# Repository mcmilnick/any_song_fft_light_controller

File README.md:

# any_song_light_controller
Send any song to a Pi, analyze the frequency spectrum, and control light strips.

This project goes with a walkthrough on my website...
https://techtures.wordpress.com/nicks-projects/any-song-christmas-lights/

By the end, you connect to your Pi via bluetooth, send any song, analyze the frenquency spectrum
of the song, and control strands of lights based of it.

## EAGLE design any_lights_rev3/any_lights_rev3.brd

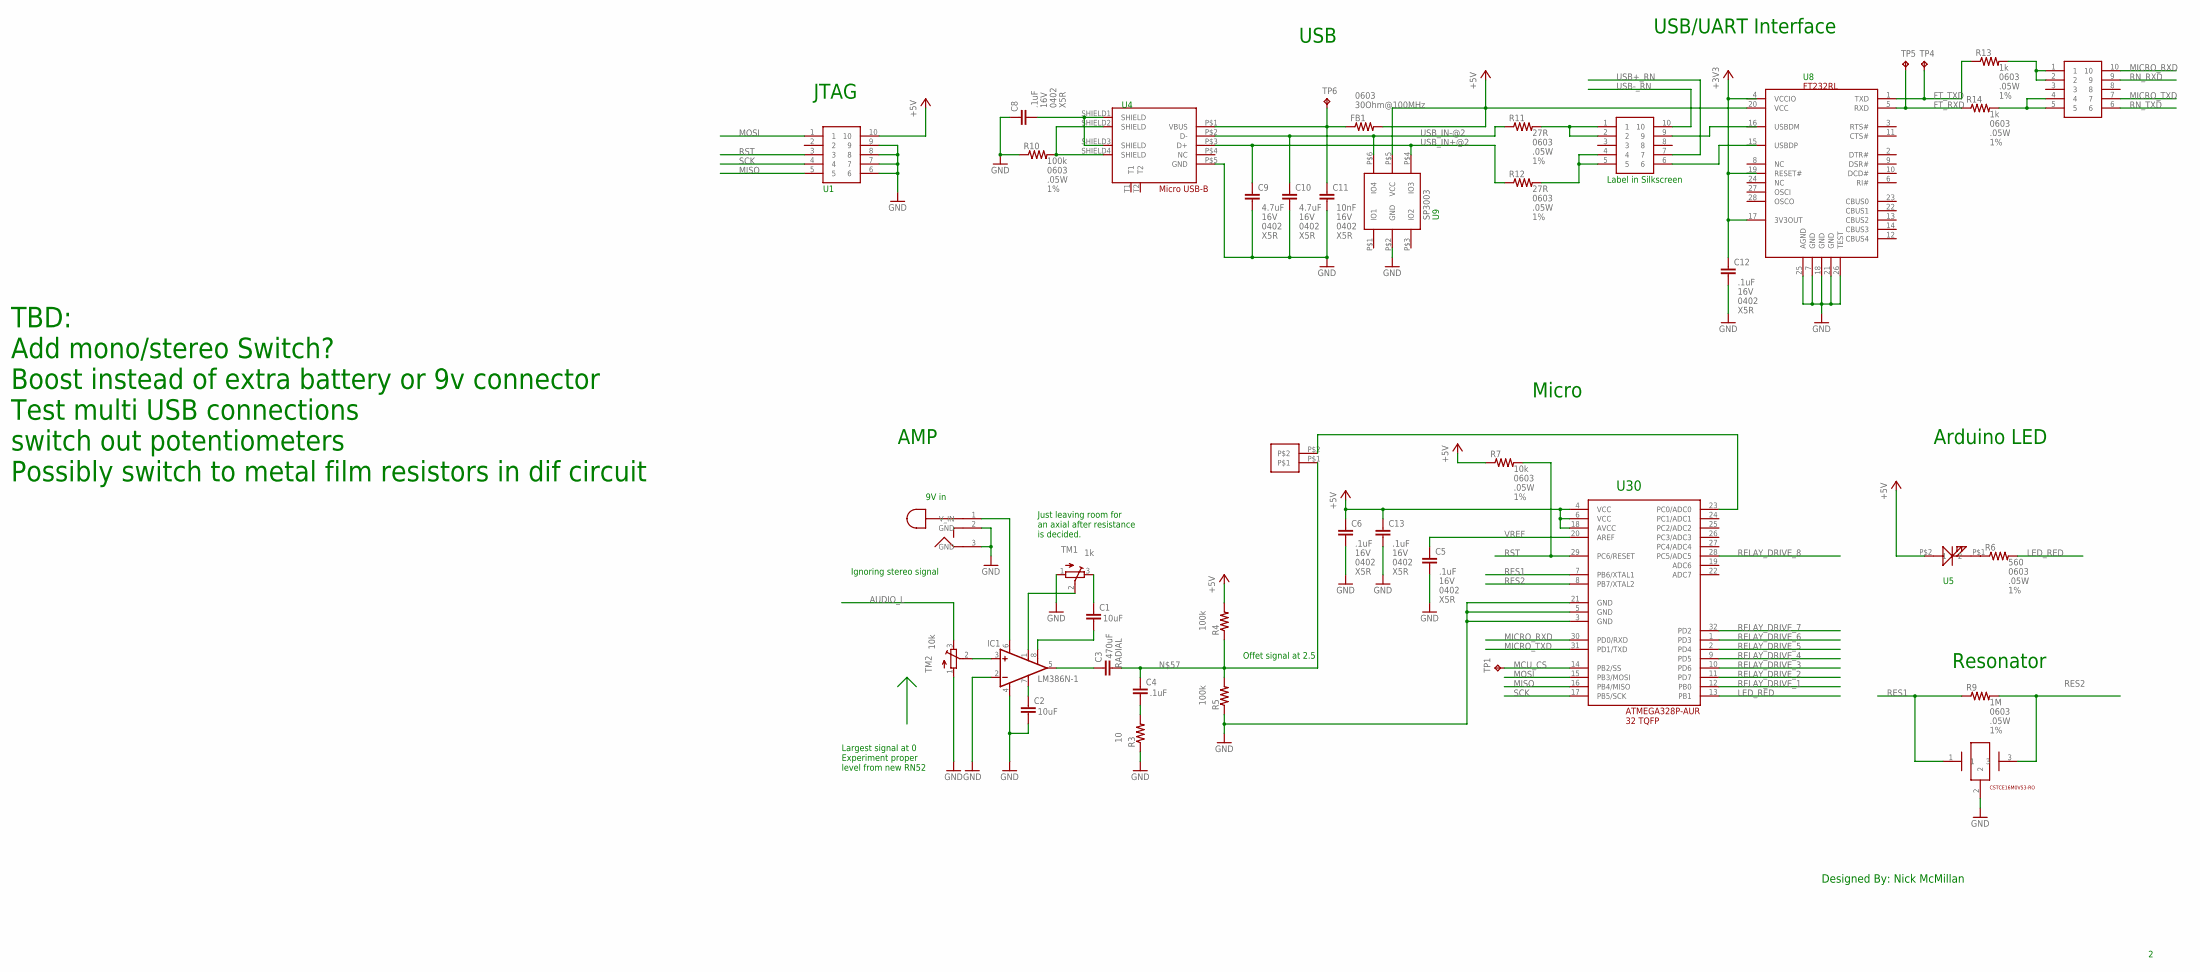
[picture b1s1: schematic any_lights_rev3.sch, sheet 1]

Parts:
C1, C2, C4: CC0603; C0603
C3: C5/3; C5B3
C5, C6, C8, C9, C10, C11, C12, C13: CC0402; C0402; RATING X5R; TOLERANCE 16V
FB1: R-US_R0603; R0603
IC1: LM386N-1; DIL08
R3, R4, R5: R-US_M0805; M0805
R6, R7, R9, R10, R11, R12, R13, R14: R-US_R0603; R0603; TOLERANCE 1%
TM1, TM2: TRIMPOT3386; TRIM-3386
TP1: TPB1,27; B1,27
TP4, TP5, TP6: TPB2,54; B2,54
U$1, U$25, U$26: 10PINHEADER
U$4: MICRO_USB_B; MICRO_USB_B_CON
U$5: SML-P11UTT86
U$6: CSTCE16M0V53-R0
U$8: FT232RL
U$9: SP3003-SC70-5; SP3003
U$29: SAMTEC2X1; 2PHEADER
U$30: ATMEGA328P-AURCT; ATMEGA328P-AURCT(32PIN)
U$40: CUI_INC_PF202A

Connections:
+3V3: C12.1, U$8.4 (VCCIO), U$8.17 (3V3OUT), U$8.19 (RESET#); also elsewhere on the board
+5V: C6.1, C13.1, FB1.2, R4.2, R7.1, U$1.10, U$5.P$2 (1), U$8.20 (VCC), U$9.P$5 (VCC), U$30.4 (VCC), U$30.6 (VCC), U$30.18 (AVCC)
AUDIO_L: TM2.3 (E); also elsewhere on the board
FT_RXD: R14.1, TP5.TP, U$8.5 (RXD)
FT_TXD: R13.1, TP4.TP, U$8.1 (TXD)
GND: C2.2, C5.2, C6.2, C8.1, C9.2, C10.2, C11.2, C12.2, C13.2, IC1.2 (-IN), IC1.4 (GND), R3.1, R5.1, R10.1, TM1.1 (A), TM2.1 (A), U$1.6, U$1.7, U$1.8, U$1.9, U$4.P$5 (GND), U$6.2, U$8.7 (GND), U$8.18 (GND), U$8.21 (GND), U$8.25 (AGND), U$8.26 (TEST), U$9.P$2 (GND), U$30.3 (GND), U$30.5 (GND), U$30.21 (GND), U$40.2 (GND), U$40.3 (GND); also elsewhere on the board
LED_RED: R6.2, U$30.13 (PB1)
MCU_CS: TP1.TP, U$30.14 (PB2/SS)
MICRO_RXD: U$26.10, U$30.30 (PD0/RXD)
MICRO_TXD: U$26.7, U$30.31 (PD1/TXD)
MISO: U$1.5, U$30.16 (PB4/MISO)
MOSI: U$1.1, U$30.15 (PB3/MOSI)
unnamed: IC1.3 (+IN), TM2.2 (S)
unnamed: C1.1, TM1.3 (E)
unnamed: IC1.1 (GAIN), TM1.2 (S)
unnamed: C2.1, IC1.7 (BYPASS)
unnamed: C1.2, IC1.8 (GAIN)
unnamed: IC1.6 (VS), U$40.1 (V_IN)
unnamed: C3.1, IC1.5 (OUT)
unnamed: R12.2, U$25.4, U$25.5
unnamed: C4.2, R3.2
unnamed: C8.2, U$4.SHIELD1 (SHIELD), U$4.SHIELD3 (SHIELD)
unnamed: R11.2, U$25.1, U$25.2
unnamed: R13.2, U$26.1, U$26.2
unnamed: R14.2, U$26.4, U$26.5
unnamed: R10.2, U$4.SHIELD2 (SHIELD), U$4.SHIELD4 (SHIELD)
unnamed: R6.1, U$5.P$1 (2)
unnamed: C3.2, C4.1, R4.1, R5.2, U$29.P$1
RELAY_DRIVE_1: U$30.12 (PB0)
RELAY_DRIVE_2: U$30.11 (PD7)
RELAY_DRIVE_3: U$30.10 (PD6)
RELAY_DRIVE_4: U$30.9 (PD5)
RELAY_DRIVE_5: U$30.2 (PD4)
RELAY_DRIVE_6: U$30.1 (PD3)
RELAY_DRIVE_7: U$30.32 (PD2)
RELAY_DRIVE_8: U$30.28 (PC5/ADC5)
RES1: R9.1, U$6.1, U$30.7 (PB6/XTAL1)
RES2: R9.2, U$6.3, U$30.8 (PB7/XTAL2)
RN_RXD: U$26.9; also elsewhere on the board
RN_TXD: U$26.6; also elsewhere on the board
RST: R7.2, U$1.3, U$30.29 (PC6/RESET)
SCK: U$1.4, U$30.17 (PB5/SCK)
SIGNAL_OUT: U$29.P$2, U$30.23 (PC0/ADC0)
USB+_FT: U$8.15 (USBDP), U$25.6
USB+_RN: U$25.7; also elsewhere on the board
USB-_FT: U$8.16 (USBDM), U$25.9
USB-_RN: U$25.10; also elsewhere on the board
USB_IN+@2: C9.1, R12.1, U$4.P$3 (D+), U$9.P$4 (IO3)
USB_IN-@2: C10.1, R11.1, U$4.P$2 (D-), U$9.P$6 (IO4)
VBUS: C11.1, FB1.1, TP6.TP, U$4.P$1 (VBUS)
VREF: C5.1, U$30.20 (AREF)

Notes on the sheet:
USB
Arduino LED
Resonator
JTAG
USB/UART Interface
Ignoring stereo signal
Largest signal at 0 Experiment proper level from new RN52
Offet signal at 2.5
Micro
AMP
Designed By: Nick McMillan
TBD: Add mono/stereo Switch? Boost instead of extra battery or 9v connector Test multi USB connections switch out potentiometers Possibly switch to metal film resistors in dif circuit
Label in Silkscreen
Just leaving room for an axial after resistance is decided.
9V in
U30

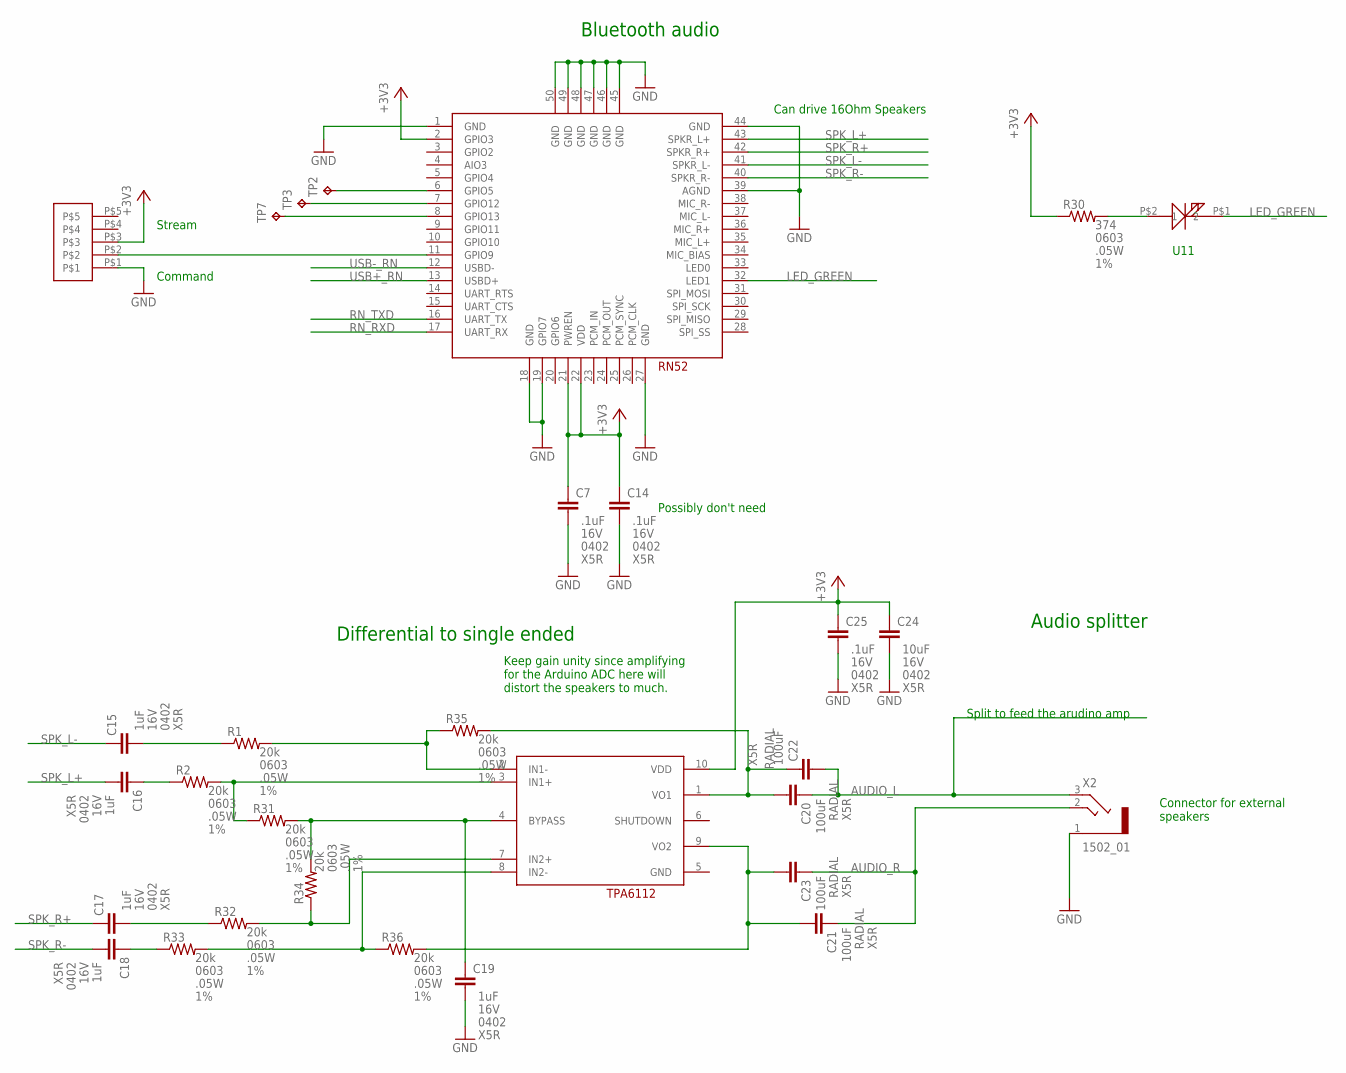
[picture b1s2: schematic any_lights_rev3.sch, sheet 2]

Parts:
C7, C14, C15, C16, C17, C18, C19, C24, C25: CC0402; C0402; RATING X5R; TOLERANCE 16V
C20, C21, C22, C23: C5/3; C5B3; RATING X5R
R1, R2, R30, R31, R32, R33, R34, R35, R36: R-US_R0603; R0603; TOLERANCE 1%
TP2, TP3, TP7: TPB1,27; B1,27
U$11: SML-P11UTT86
U$23: RN52
U$27: SAMTEC1X5; 5XHEADER
U$28: TPA6112
X2: 1502_01

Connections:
+3V3: C7.1, C14.1, C24.1, C25.1, R30.1, U$23.2 (GPIO3), U$23.21 (PWREN), U$23.22 (VDD), U$27.P$3, U$28.10 (VDD); also elsewhere on the board
AUDIO_L: C20.1, C22.2, X2.3 (2); also elsewhere on the board
AUDIO_R: C21.1, C23.1, X2.2 (3)
GND: C7.2, C14.2, C19.2, C24.2, C25.2, U$23.1 (GND), U$23.18 (GND), U$23.19 (GPIO7), U$23.27 (GND), U$23.39 (AGND), U$23.44 (GND), U$23.45 (GND), U$23.46 (GND), U$23.47 (GND), U$23.48 (GND), U$23.49 (GND), U$23.50 (GND), U$27.P$1, X2.1; also elsewhere on the board
LED_GREEN: U$11.P$1 (2), U$23.32 (LED1)
unnamed: R30.2, U$11.P$2 (1)
unnamed: U$23.11 (GPIO9), U$27.P$2
unnamed: R1.2, R35.1, U$28.2 (IN1-)
unnamed: TP2.TP, U$23.6 (GPIO5)
unnamed: TP3.TP, U$23.7 (GPIO12)
unnamed: TP7.TP, U$23.8 (GPIO13)
unnamed: C15.2, R1.1
unnamed: R2.2, R31.1, U$28.3 (IN1+)
unnamed: C16.1, R2.1
unnamed: R32.2, R34.1, U$28.7 (IN2+)
unnamed: R33.2, R36.1, U$28.8 (IN2-)
unnamed: C18.1, R33.1
unnamed: C17.2, R32.1
unnamed: C19.1, R31.2, R34.2, U$28.4 (BYPASS)
unnamed: C20.2, C22.1, R35.2, U$28.1 (VO1)
unnamed: C21.2, C23.2, R36.2, U$28.9 (VO2)
RN_RXD: U$23.17 (UART_RX); also elsewhere on the board
RN_TXD: U$23.16 (UART_TX); also elsewhere on the board
SPK_L+: C16.2, U$23.43 (SPKR_L+)
SPK_L-: C15.1, U$23.41 (SPKR_L-)
SPK_R+: C17.1, U$23.42 (SPKR_R+)
SPK_R-: C18.2, U$23.40 (SPKR_R-)
USB+_RN: U$23.13 (USBD+); also elsewhere on the board
USB-_RN: U$23.12 (USBD-); also elsewhere on the board

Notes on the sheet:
Bluetooth audio
Differential to single ended
Can drive 16Ohm Speakers
Stream
Command
Possibly don't need
Connector for external speakers
Split to feed the arudino amp
Keep gain unity since amplifying for the Arduino ADC here will distort the speakers to much.
Audio splitter
U11

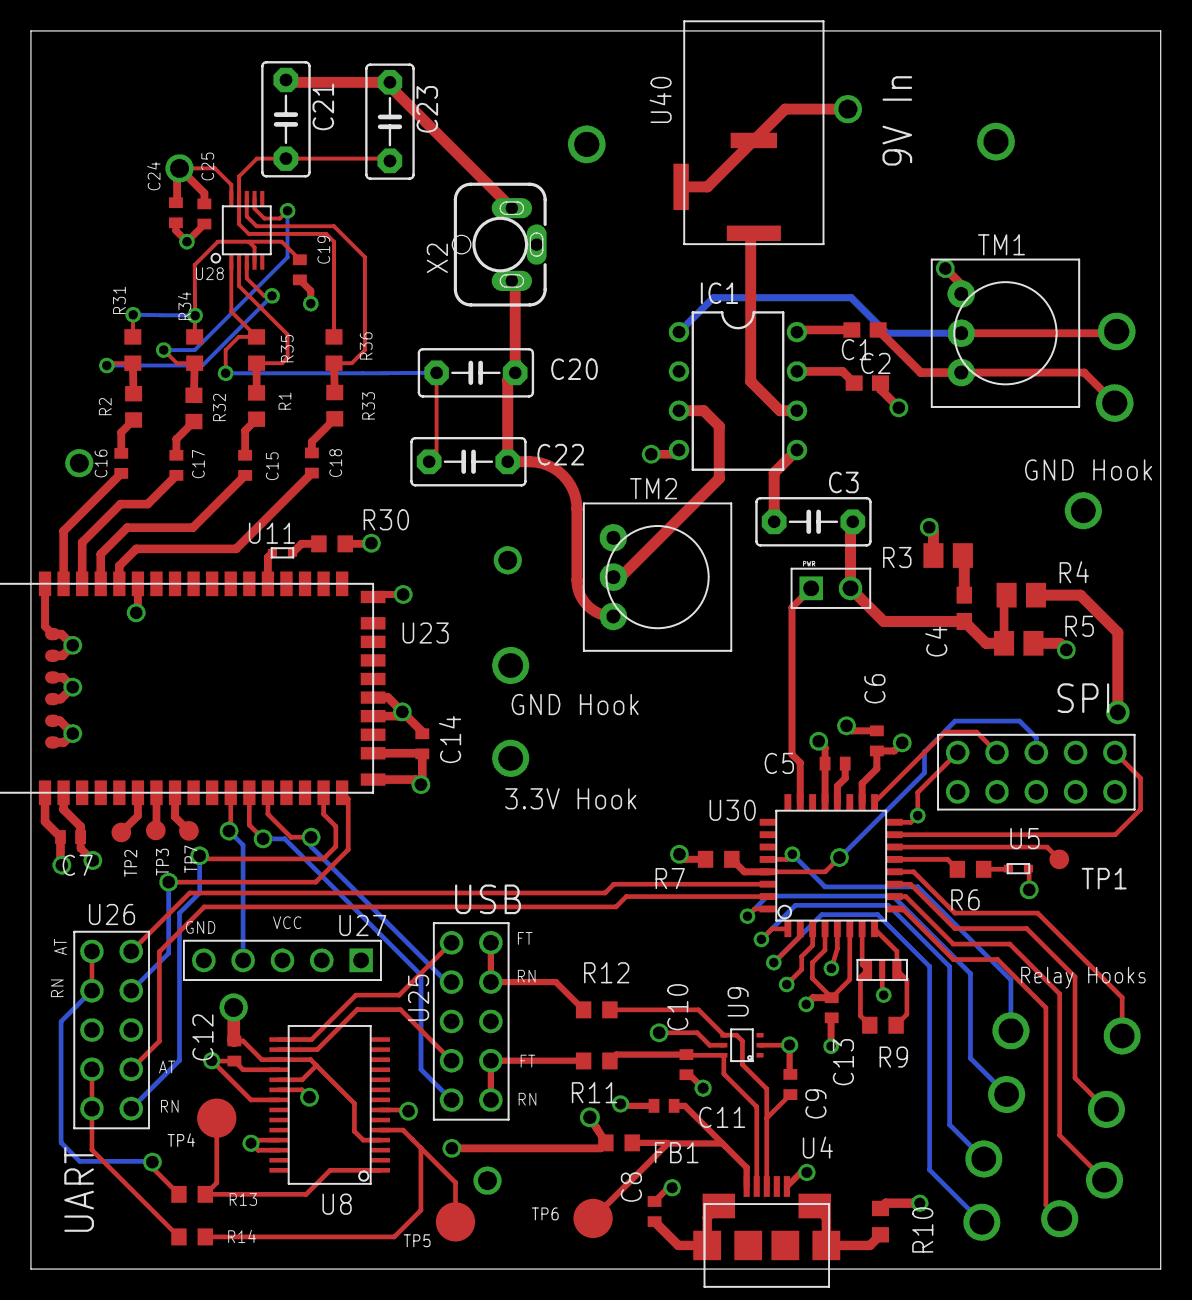
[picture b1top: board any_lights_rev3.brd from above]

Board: 4 copper layers, 73.0 x 80.0 mm, 72 parts (0 on the bottom side), 65 nets.

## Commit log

2016-02-05 Adding schematic and simulation
2016-02-05 Schematic didn't upload correctly
2016-02-05 Adding schematic reduced size
2016-02-05 adding arduino code
2016-02-08 Modified Goertzel algorithm with floating point. Would like to get rid of this, but precision is necessary for now and the code is already fast enough. Also added pin drive portion depending on the m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
2016-02-09 changed arduino code
    Cut debug and changed the trigger magnitude.
2016-03-08 Spinning a custom board
    Added initial consolidated schematic and PCB as rev2 and cheap proto
    version as rev3. Also includes BOMs for both.
